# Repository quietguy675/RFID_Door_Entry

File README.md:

# RFID_Door_Entry
Arduino-based system which interacts with an HID reader, a SD card shield, and an electric door strike

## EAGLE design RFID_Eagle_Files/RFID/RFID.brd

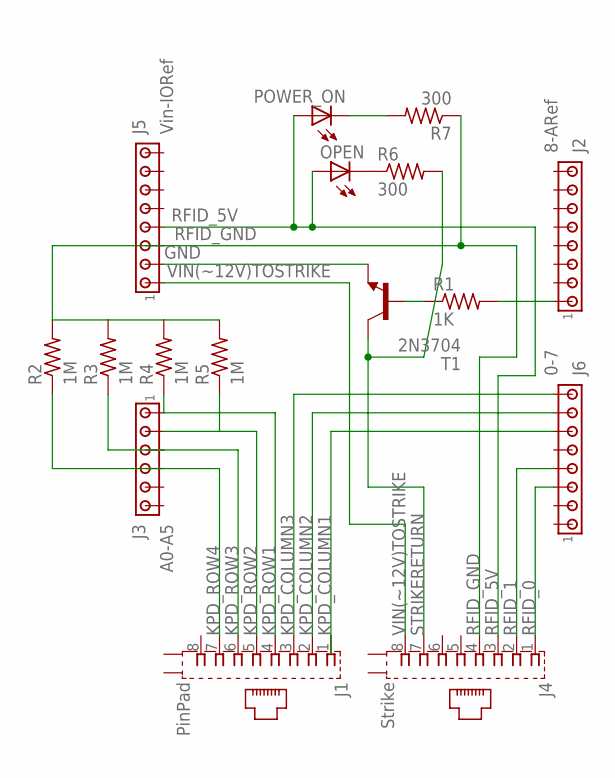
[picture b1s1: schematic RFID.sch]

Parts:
J1: PinPad; 556591-1
J2: 8-ARef; 1X8MTA
J3: A0-A5; 10X06MTA
J4: Strike; 556591-1
J5: Vin-IORef; 1X8MTA
J6: 0-7; 1X8MTA
OPEN: LED3MM
POWER_ON: LED3MM
R1: 1K; 0204/5
R2, R3, R4, R5: 1M; 0204/5
R6, R7: 300; 0204/5
T1: 2N3704; TO92

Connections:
GND: J5.2, T1.3 (E)
KPD_COLUMN1: J6.6
KPD_COLUMN2: J1.2, J6.7
KPD_COLUMN3: J1.3, J6.8
KPD_ROW1: J1.4, J3.6 (1), R4.1
KPD_ROW2: J1.5, J3.5 (2), R5.1
KPD_ROW3: J1.6, J3.4 (3), R3.1
KPD_ROW4: J1.7, J3.3 (4), R2.1
unnamed: J2.1, R1.2
unnamed: R1.1, T1.1 (B)
unnamed: OPEN.K (C), R6.1
unnamed: POWER_ON.K (C), R7.2
RFID_0: J4.1, J6.3
RFID_1: J4.2, J6.4
RFID_5V: J4.3, J5.4, OPEN.A, POWER_ON.A
RFID_GND: J4.4, J5.3, R2.2, R3.2, R4.2, R5.2, R7.1
STRIKERETURN: J4.7, R6.2, T1.2 (C)
VIN(~12V)TOSTRIKE: J4.8, J5.1

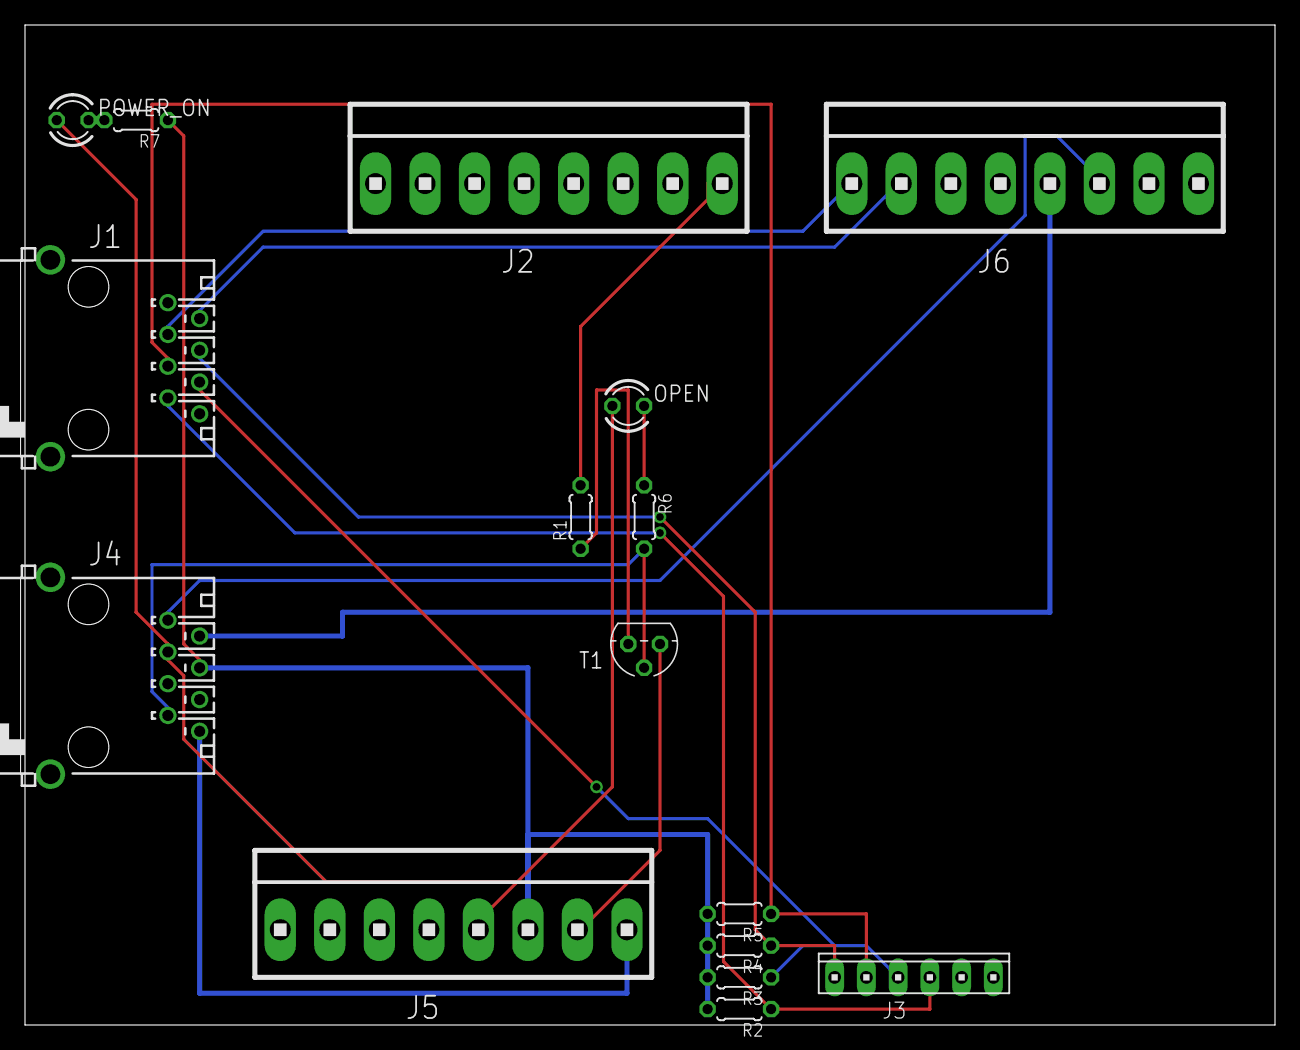
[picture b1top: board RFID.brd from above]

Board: 2 copper layers, 100.0 x 80.0 mm, 16 parts (0 on the bottom side), 17 nets.

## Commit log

2017-01-31 Fixed issues in the ISR and some other logic comparisons.
